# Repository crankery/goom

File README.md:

# Goom VCF

Goom is yet another Moog style transistor ladder VCF for Eurorack. It's setup to be a fairly shallow 14hp module.

This is mainly a re-layout of [Yves Usson's](http://yusynth.net/) [YuSynth MiniMoog VCF](http://yusynth.net/Modular/index_en.html). A few substitions of really super obsolete componetns with only somewhat obsolete components were made. Everything is through-hole mount, I haven't made the leap to SMT yet. There's similar designs using SMT devices out there; just search for "minimoog transistor ladder filter eurorack".

The original design was for a 5U modular synth because that's what Yves was building. You can still [buy the YuSynth PCB](https://www.soundtronics.co.uk/yusynth-diy-synth/) and adapt it to Eurorack power and figure out how to attach it to a front panel but it's really designed to be a MOTM module. 

This used three matched pairs of [BC547C NPN transistors](Documents/BC547.pdf), a [BC557C PNP transistor](Documents/BC557.pdf), a [TL072 op-amp](Documents/tl072h.pdf) and two [CA3046N transistor arrays](Documents/CA3046N.pdf). Of these components, the CA3056 and TL072 are still readily available. There's a clear substition for the transistors as well as a possible better option. The original design was for $\pm15V$; Yves suggests some resistor value changes for Eurorack's $\pm12V$ power. Matching transistors is still possible in this day and age but I felt like it was a pain so I decided to try out another option.

## Changes from YuSynth Design

You can still easily obtain BC5x7 transistors but I happened to have a bunch of 2N3904 and 2N3906 transistors on hand so I elected to use those. Then I decided trying to match pairs of them was a pain. Knowing the [Alfa RPAR AS394](https://www.alfarzpp.lv/eng/sc/AS394CH.pdf) matched transistor pair IC was available, I decided to try that out.
I've left the discrete transistor pads on the PCB.

The 2N3904 is standing in for the BC557, 2N3096 for the BC547N transistors.

Since the AS394 has internal diodes coming off the emitters, I've included pads for 2N4148 diodes on the optional discrete transistor pads. Again, 2N2148 was selected because I had them on hand.

## Design Constraints

The PCB is 100mm in the long dimension which makes it pretty darned cheap to order from [PCBWay](https://www.pcbway.com/). It is 70.8mm wide which [Doepfer says is 14hp](https://doepfer.de/a100_man/a100m_e.htm).

I elected to exclusively use through-hole components and PCB mount vertical potentiometers and jacks. Because some of these components are taller than the jacks and pots most of the components are on the opposite side of the PCB from the components that protrude from the front panel.

The potentiometers used are Alpha RD901F style 9mm vertical PCB mount with 6.35mm (1/4") round shafts and threaded collar to attach the front panel. The 10KΩ anti-log taper potentiometer was not available in this style so I used the RD901F which has a 6mm 18 tooth plastic shaft for resonance/emphasis. The jacks are PJ301BM 3.5mm switched tip mono jacks.

## Parts Sourcing

Most of the hardware and the discrete components were obtained from [Tayda](https://www.taydaelectronics.com/). The AS3046 & AS394 ICs are from [Cabintech](https://cabintechglobal.com/). The TL072 ICs were from either Mouser or Digi-key.

# Design

I started out by re-drawing the original design in [KiCad](https://www.kicad.org).

## To Do

- [ ] A note on the schematic `** resistor valus to be adjusted to adapt to input and output levels` which applies to R5 and R32. Not sure what the appropriate values are for Eurorack levels and this isn't discussed anywhere on the page
- [ ] The references are different in the KiCad schematic vs the original. Make them match
- [ ] The BOM says `47nF matched to 1%` for C4-7, not sure how to go about that

## Changes From Original

- R24, R27, R26 value changed for $\pm12V$
- Eliminated the MOTM power connection and switched all the $\pm15V$ to $\pm12V$
- Added a Eurorack 10 pin header power connector
- Switched the 3 x 100KΩ resistors to a 4 pin resistor network
- Switched the 4 x 470Ω resistors to an 8 pin isolated resistor pack 
- Added diodes off the matched transitor emitters as per the AS394's internals
- Added optional AS394 ICs to replace the matched transistors

# Front Panel

I'm trying to put the edge cuts for the panel, including jack and pot holes on a user layer. The graphics for the front panel are on another one.

## To Do

- [ ] determine how one goes about exporting a document to send to a service to get panels cut and drilled
- [ ] in the meantime, determine how to export the panel edge cuts layer to a pdf so the holes can be accurately drilled by hand in a blank panel
- [ ] determine how to go about exporting the graphics layer and doing some sort of acid etching process or something

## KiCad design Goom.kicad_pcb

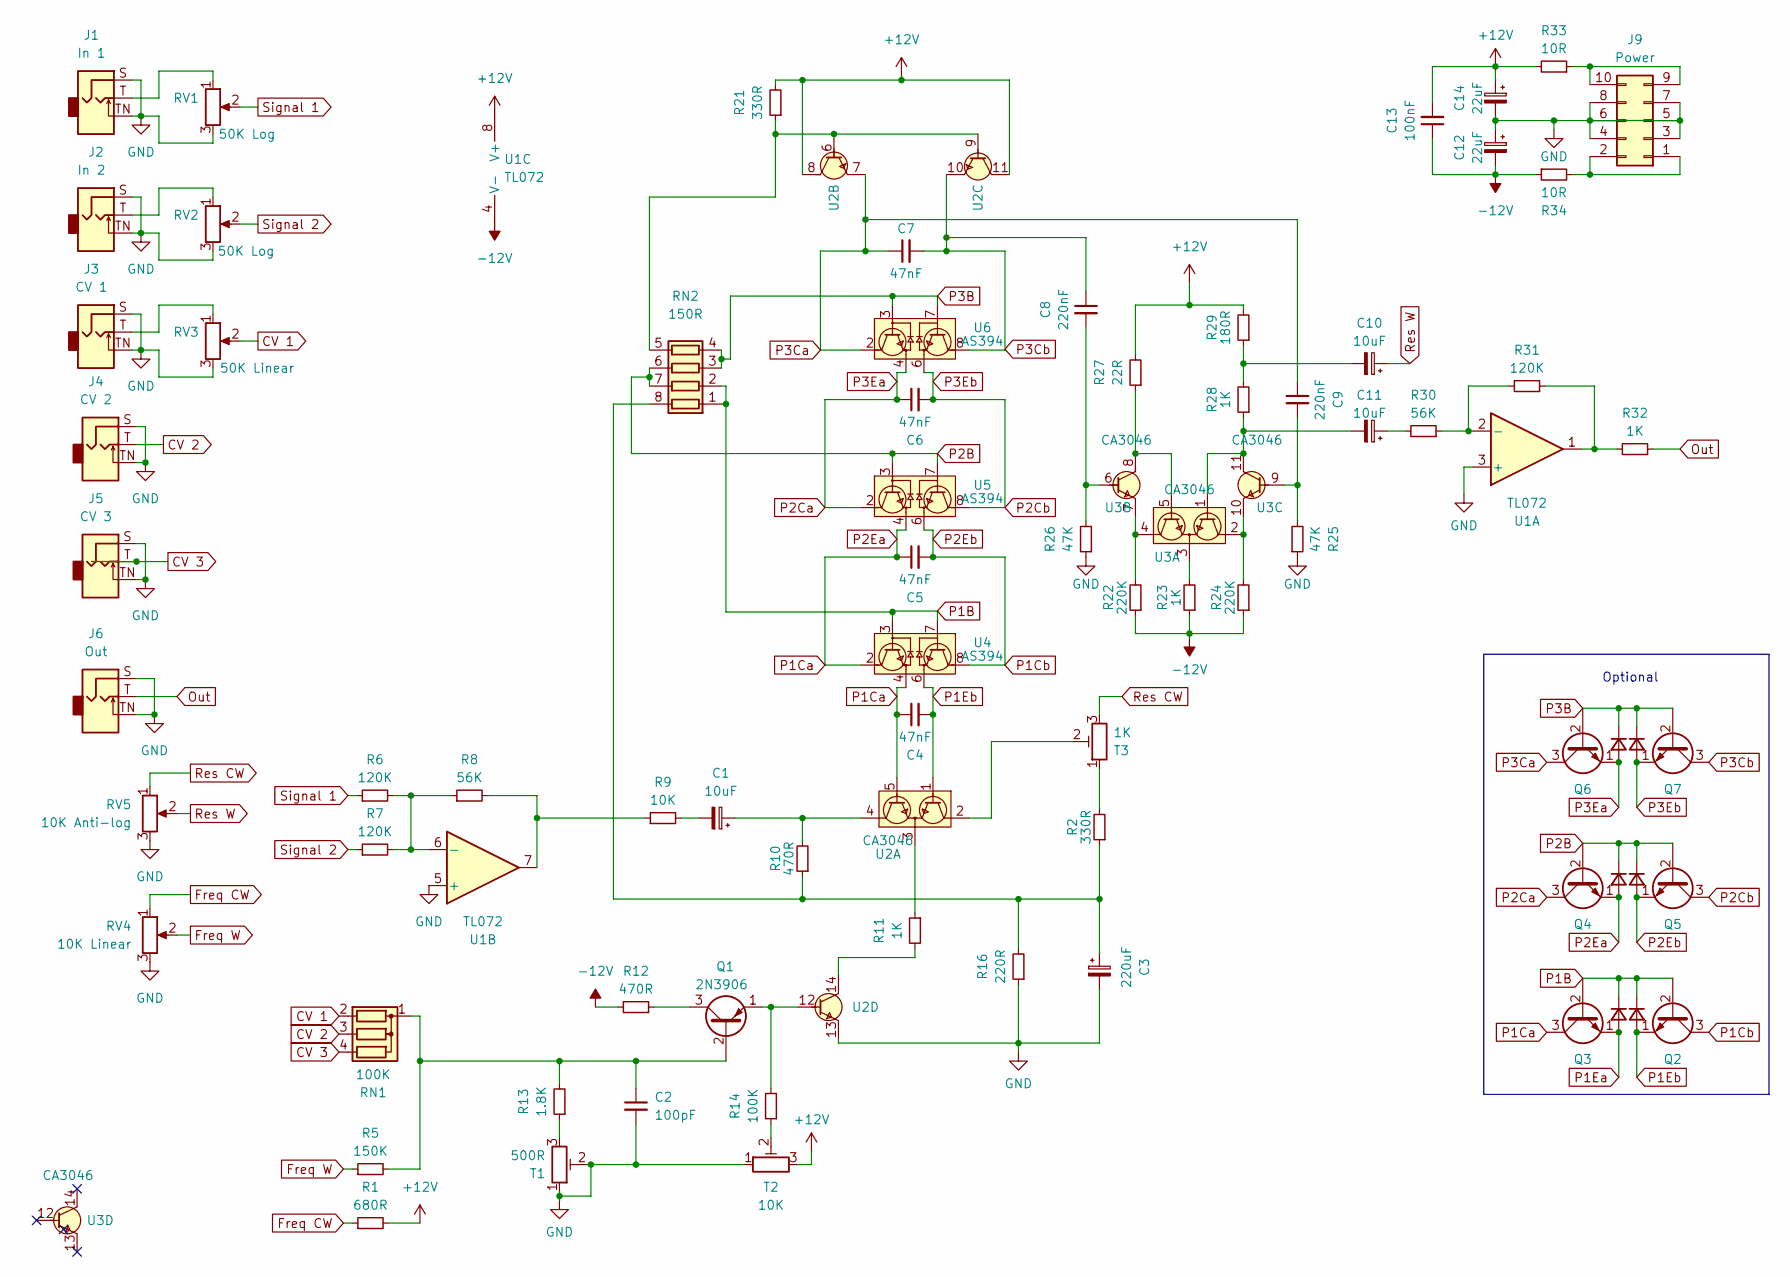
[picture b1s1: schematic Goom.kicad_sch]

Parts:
C1, C10, C11: 10uF; CP_Radial_D5.0mm_P2.50mm
C2: 100pF; C_Disc_D3.0mm_W2.0mm_P2.50mm
C3: 220uF; CP_Radial_D5.0mm_P2.50mm
C4, C5, C6, C7: 47nF; C_Rect_L7.2mm_W2.5mm_P5.00mm_FKS2_FKP2_MKS2_MKP2
C8, C9: 220nF; C_Rect_L7.2mm_W2.5mm_P5.00mm_FKS2_FKP2_MKS2_MKP2
C12, C14: 22uF; CP_Radial_D5.0mm_P2.50mm
C13: 100nF; C_Rect_L7.2mm_W2.5mm_P5.00mm_FKS2_FKP2_MKS2_MKP2
D1, D2, D3, D4, D5, D6: 2N4148; D_DO-35_SOD27_P7.62mm_Horizontal
J1: In 1; Jack_3.5mm_QingPu_WQP-PJ301BM_Vertical
J2: In 2; Jack_3.5mm_QingPu_WQP-PJ301BM_Vertical
J3: CV 1; Jack_3.5mm_QingPu_WQP-PJ301BM_Vertical
J4: CV 2; Jack_3.5mm_QingPu_WQP-PJ301BM_Vertical
J5: CV 3; Jack_3.5mm_QingPu_WQP-PJ301BM_Vertical
J6: Out; Jack_3.5mm_QingPu_WQP-PJ301BM_Vertical
J9: Power; IDC-Header_2x05_P2.54mm_Vertical
Q1: 2N3906; TO-92_Inline
Q2, Q3, Q4, Q5, Q6, Q7: 2N3904; TO-92_Inline
R1: 680R; R_Axial_DIN0204_L3.6mm_D1.6mm_P5.08mm_Horizontal
R2, R21: 330R; R_Axial_DIN0204_L3.6mm_D1.6mm_P5.08mm_Horizontal
R5: 150K; R_Axial_DIN0204_L3.6mm_D1.6mm_P5.08mm_Horizontal
R6, R7, R31: 120K; R_Axial_DIN0204_L3.6mm_D1.6mm_P5.08mm_Horizontal
R8, R30: 56K; R_Axial_DIN0204_L3.6mm_D1.6mm_P5.08mm_Horizontal
R9: 10K; R_Axial_DIN0204_L3.6mm_D1.6mm_P5.08mm_Horizontal
R10, R12: 470R; R_Axial_DIN0204_L3.6mm_D1.6mm_P5.08mm_Horizontal
R11, R23, R28, R32: 1K; R_Axial_DIN0204_L3.6mm_D1.6mm_P5.08mm_Horizontal
R13: 1.8K; R_Axial_DIN0204_L3.6mm_D1.6mm_P5.08mm_Horizontal
R14: 100K; R_Axial_DIN0204_L3.6mm_D1.6mm_P5.08mm_Horizontal
R16: 220R; R_Axial_DIN0204_L3.6mm_D1.6mm_P5.08mm_Horizontal
R22, R24: 220K; R_Axial_DIN0204_L3.6mm_D1.6mm_P5.08mm_Horizontal
R25, R26: 47K; R_Axial_DIN0204_L3.6mm_D1.6mm_P5.08mm_Horizontal
R27: 22R; R_Axial_DIN0204_L3.6mm_D1.6mm_P5.08mm_Horizontal
R29: 180R; R_Axial_DIN0204_L3.6mm_D1.6mm_P5.08mm_Horizontal
R33, R34: 10R; R_Axial_DIN0204_L3.6mm_D1.6mm_P5.08mm_Horizontal
RN1: 100K; R_Array_SIP4
RN2: 150R; R_Array_SIP8
RV1, RV2: 50K Log; Potentiometer_Alpha_RD901F-40-00D_Single_Vertical
RV3: 50K Linear; Potentiometer_Alpha_RD901F-40-00D_Single_Vertical
RV4: 10K Linear; Potentiometer_Alpha_RD901F-40-00D_Single_Vertical
RV5: 10K Anti-log; Potentiometer_Alpha_RD901F-40-00D_Single_Vertical
T1: 500R; Potentiometer_Bourns_3266Y_Vertical
T2: 10K; Potentiometer_Bourns_3386P_Vertical
T3: 1K; Potentiometer_Bourns_3386P_Vertical
U1: TL072; DIP-8_W7.62mm
U2, U3: CA3046; DIP-14_W7.62mm
U4, U5, U6: AS394; TO-5-8

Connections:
+12V: C13.2, C14.1, R1.2, R21.2, R27.2, R29.2, R33.2, T2.3, U1.8 (V+), U2.8 (Q3C), U2.11 (Q4C)
-12V: C12.2, C13.1, R12.2, R22.1, R23.1, R24.1, R34.1, U1.4 (V-)
CV 1: RN1.2 (R1), RV3.2
CV 2: J4.T, RN1.3 (R2)
CV 3: J5.T, RN1.4 (R3)
Freq CW: R1.1, RV4.1
Freq W: R5.1, RV4.2
GND: C2.2, C3.2, C12.1, C14.2, J1.S, J1.TN, J2.S, J2.TN, J3.S, J3.TN, J4.S, J4.TN, J5.S, J5.TN, J6.S, J6.TN, J9.3, J9.4, J9.5, J9.6, J9.7, J9.8, R16.1, R25.1, R26.1, RV1.3, RV2.3, RV3.3, RV4.3, RV5.3, T1.1, T1.2, T2.1, U1.3 (+), U1.5 (+), U2.13 (Q5E)
unnamed: C1.2, R9.2
unnamed: C10.2, R28.2, R29.1
unnamed: C11.1, R30.2
unnamed: J1.T, RV1.1
unnamed: J2.T, RV2.1
unnamed: J3.T, RV3.1
unnamed: J9.1, J9.2, R34.2
unnamed: J9.9, J9.10, R33.1
unnamed: C2.1, Q1.2 (B), R5.2, R13.2, RN1.1 (common)
unnamed: Q1.3 (C), R12.1
unnamed: Q1.1 (E), R14.2, U2.12 (Q5B)
unnamed: R2.2, T3.1
unnamed: R8.2, R9.1, U1.7
unnamed: R13.1, T1.3
unnamed: R14.1, T2.2
unnamed: R31.1, R32.2, U1.1
unnamed: C3.1, R2.1, R10.1, R16.2, RN2.8 (R1.2)
unnamed: R21.1, RN2.5 (R4.2), U2.6 (Q3B), U2.9 (Q4B)
unnamed: R30.1, R31.2, U1.2 (-)
unnamed: R6.2, R7.2, R8.1, U1.6 (-)
unnamed: T3.2, U2.2 (Q1B)
unnamed: R11.1, U2.3 (Q1/Q2E)
unnamed: C1.1, R10.2, U2.4 (Q2B)
unnamed: R11.2, U2.14 (Q5C)
unnamed: R24.2, U3.2 (Q1B), U3.10 (Q4E)
unnamed: C11.2, R28.1, U3.1 (Q1C), U3.11 (Q4C)
unnamed: R23.2, U3.3 (Q1/Q2E)
unnamed: R22.2, U3.4 (Q2B), U3.7 (Q3E)
unnamed: R27.1, U3.5 (Q2C), U3.8 (Q3C)
unnamed: C8.2, R26.2, U3.6 (Q3B)
unnamed: C9.2, R25.2, U3.9 (Q4B)
Out: J6.T, R32.1
P1B: D1.1 (K), D2.1 (K), Q2.2 (B), Q3.2 (B), RN2.1 (R1.1), RN2.2 (R2.1), U4.3 (Q1/Q2E), U4.7 (Q2B)
P1Ca: C4.1, C5.1, D3.2 (A), Q3.3 (C), Q4.1 (E), U2.5 (Q2C), U4.2 (Q1B), U4.4 (Q1C), U5.4 (Q1C)
P1Cb: C5.2, D4.2 (A), Q2.3 (C), Q5.1 (E), U4.8 (Q2B), U5.6 (Q1C)
P1Ea: D2.2 (A), Q3.1 (E)
P1Eb: C4.2, D1.2 (A), Q2.1 (E), U2.1 (Q1C), U4.6 (Q1C)
P2B: D3.1 (K), D4.1 (K), Q4.2 (B), Q5.2 (B), RN2.6 (R3.2), RN2.7 (R2.2), U5.3 (Q1/Q2E), U5.7 (Q2B)
P2Ca: C6.1, D5.2 (A), Q4.3 (C), Q6.1 (E), U5.2 (Q1B), U6.4 (Q1C)
P2Cb: C6.2, D6.2 (A), Q5.3 (C), Q7.1 (E), U5.8 (Q2B), U6.6 (Q1C)
P3B: D5.1 (K), D6.1 (K), Q6.2 (B), Q7.2 (B), RN2.3 (R3.1), RN2.4 (R4.1), U6.3 (Q1/Q2E), U6.7 (Q2B)
P3Ca: C7.1, C9.1, Q6.3 (C), U2.7 (Q3E), U6.2 (Q1B)
P3Cb: C7.2, C8.1, Q7.3 (C), U2.10 (Q4E), U6.8 (Q2B)
Res CW: RV5.1, T3.3
Res W: C10.1, RV5.2
Signal 1: R6.1, RV1.2
Signal 2: R7.1, RV2.2

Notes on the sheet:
Optional

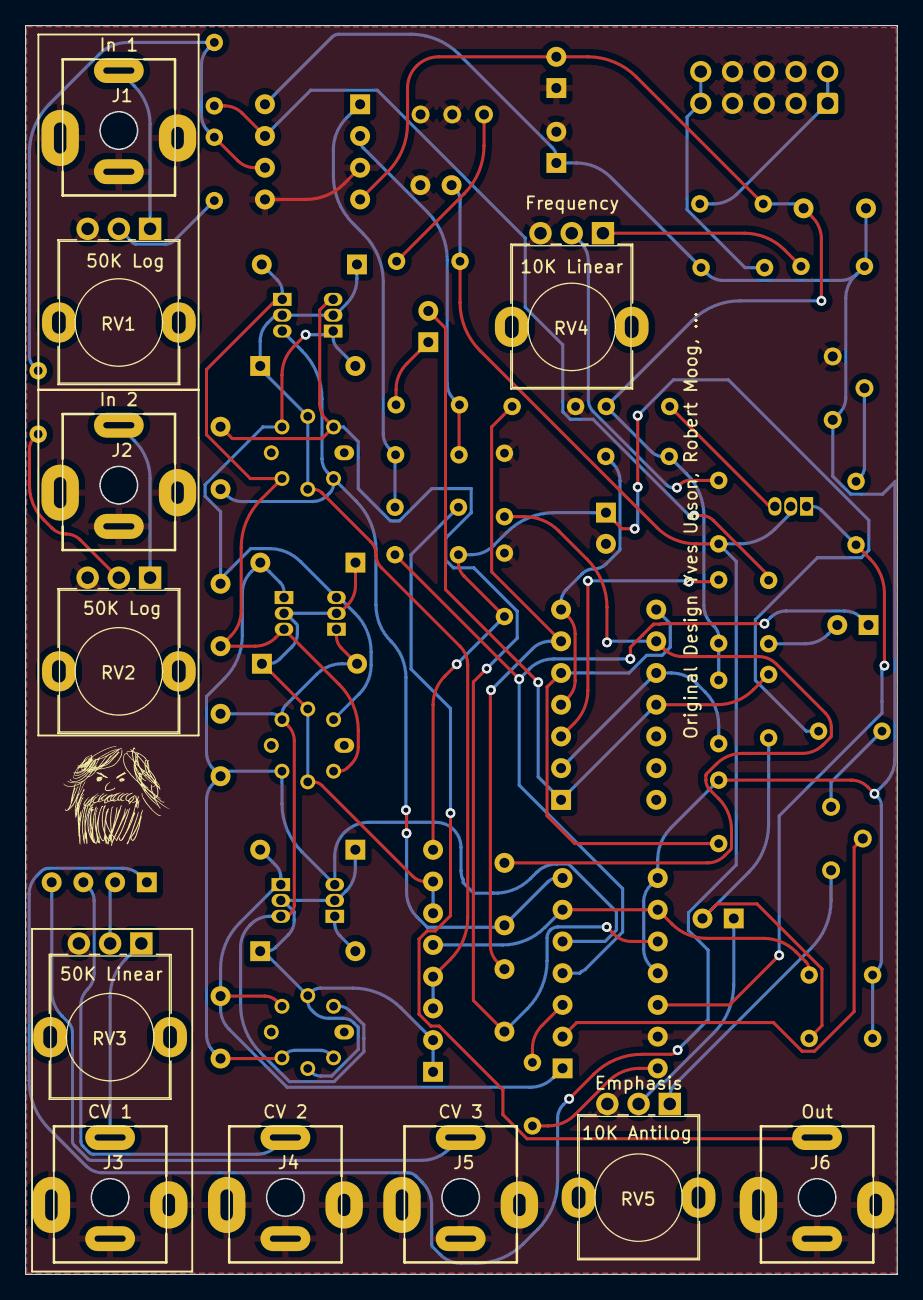
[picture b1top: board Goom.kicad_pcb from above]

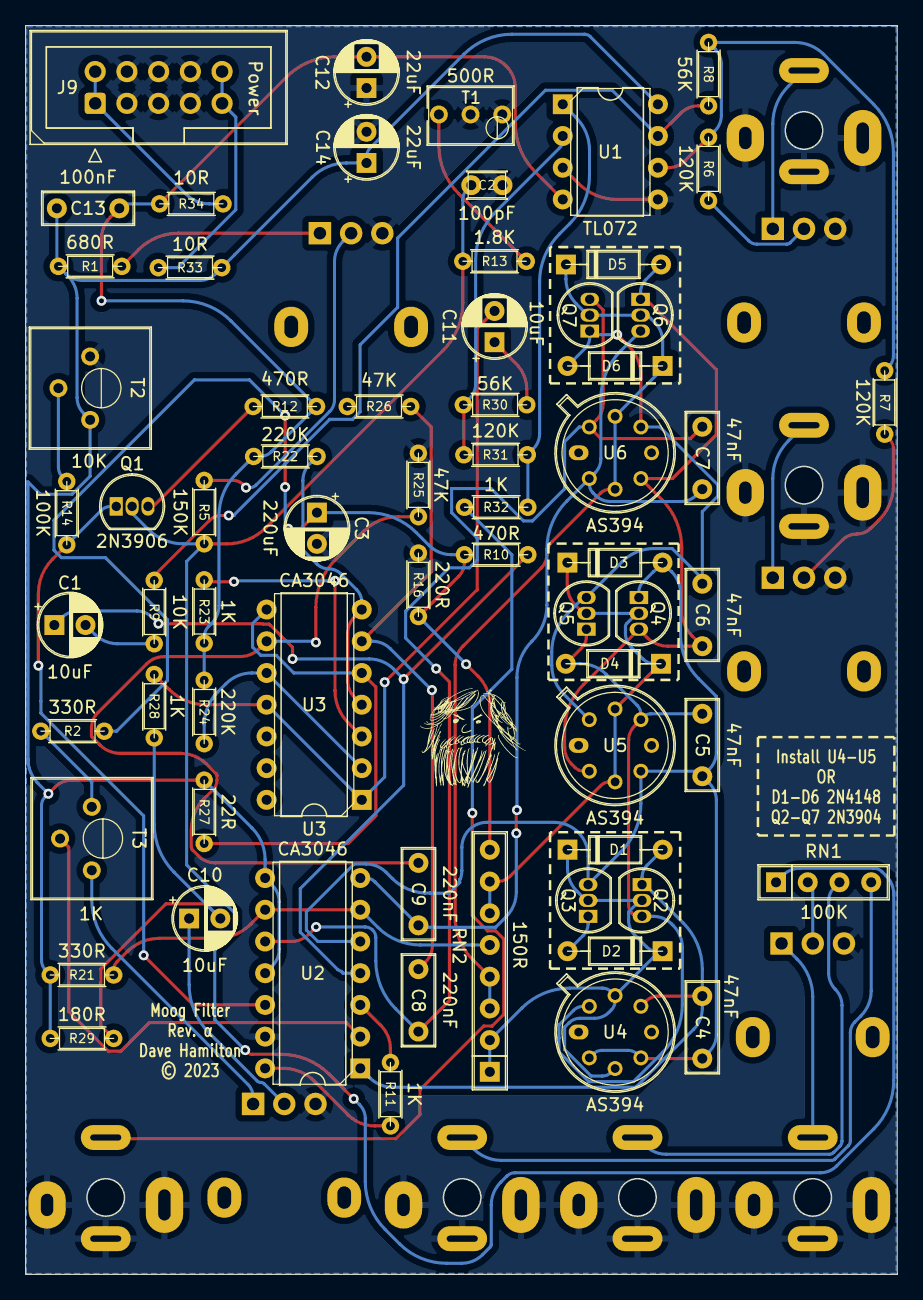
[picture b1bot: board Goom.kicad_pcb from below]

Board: 2 copper layers, 69.8 x 100.0 mm, 77 parts (66 on the bottom side), 55 nets.

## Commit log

2023-07-20 yeah, i should have done this a while ago
2023-07-20 clean up
2023-07-20 symbols folder
2023-07-20 rename
2023-07-20 add various reference docs
2023-07-20 fixing links
2023-08-02 clean up again
2023-08-02 add some gerbers

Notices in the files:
Goom.kicad_pcb:
© 2023
